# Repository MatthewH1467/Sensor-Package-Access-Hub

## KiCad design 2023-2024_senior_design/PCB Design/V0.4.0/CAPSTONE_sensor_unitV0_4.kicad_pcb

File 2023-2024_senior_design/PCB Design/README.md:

# PCB Design

## V0.3.0
* All components on board

## V0.4.0
* Add holes for standoffs
* Compress board size
* Added silkscreen logo, designer names, part names, version number, 
* Add a ground plane
* Different footprint for Teensy

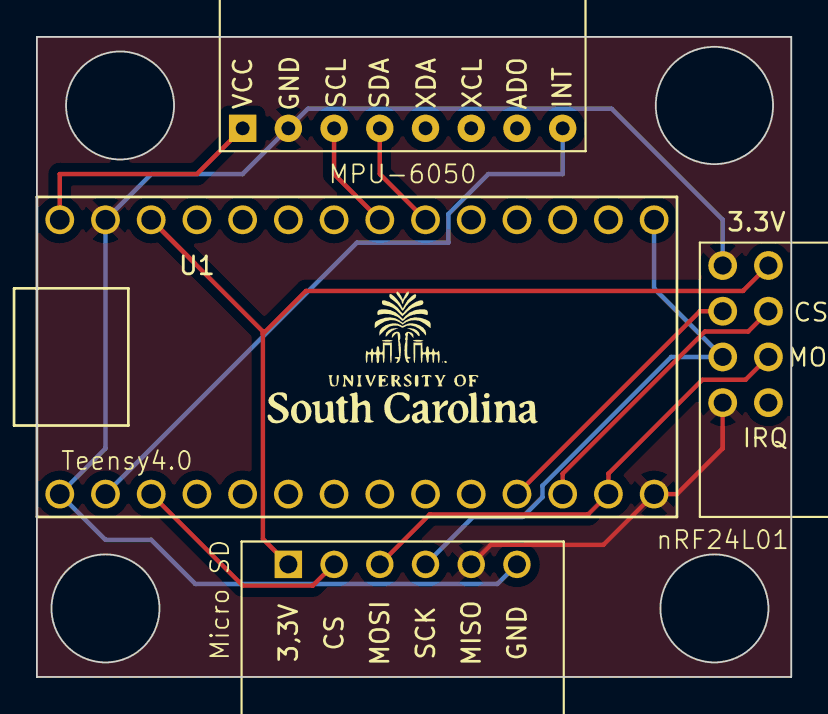
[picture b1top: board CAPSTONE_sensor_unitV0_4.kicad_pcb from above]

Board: 2 copper layers, 41.9 x 35.6 mm, 4 parts (0 on the bottom side), 12 nets.

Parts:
MPU-6050: MPU6050_Module; MPU6050_Sensor_package_edit
Micro SD: microSD_small-ARTS-Lab; small_microSD_sensor_package_edit
U1: Teensy4.0-teensy-ARTS-Lab; Teensy40_sensor_package_edit
nRF24L01: nRF24L01+-ARTS-Lab; nRF24L01+_sensor_package_edit_V0_2

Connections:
GND: MPU-6050.2 (GND), Micro SD.6 (GND), U1.1 (GND), U1.32 (GND), nRF24L01.5 (GND)
unnamed: MPU-6050.8 (INT), U1.2 (0_RX1_CRX2_CS1)
unnamed: MPU-6050.3 (SCL), U1.26 (19_A5_SCL0)
unnamed: MPU-6050.4 (SDA), U1.25 (18_A4_SDA0)
unnamed: MPU-6050.1 (VCC), U1.33 (VIN)
unnamed: Micro SD.1 (3.3V), U1.31 (3V3), nRF24L01.1 (3.3V)
unnamed: Micro SD.4 (CLK), U1.20 (13_SCK_CRX1_LED), nRF24L01.7 (SCK)
unnamed: Micro SD.2 (CS), U1.3 (1_TX1_CTX2_MISO1)
unnamed: Micro SD.5 (MISO), U1.14 (12_MISO_MQSL), nRF24L01.8 (MISO)
unnamed: Micro SD.3 (MOSI), U1.13 (11_MOSI_CTX1), nRF24L01.3 (MOSI)
unnamed: U1.11 (9_OUT1C), nRF24L01.6 (CE)
unnamed: U1.12 (10_CS_MQSR), nRF24L01.2 (CSN)

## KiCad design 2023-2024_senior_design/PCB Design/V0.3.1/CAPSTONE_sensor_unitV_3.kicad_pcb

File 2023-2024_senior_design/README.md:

# Sensor-Package-Access-Hub (2023-2024 Senior Design Project)
1. xxx

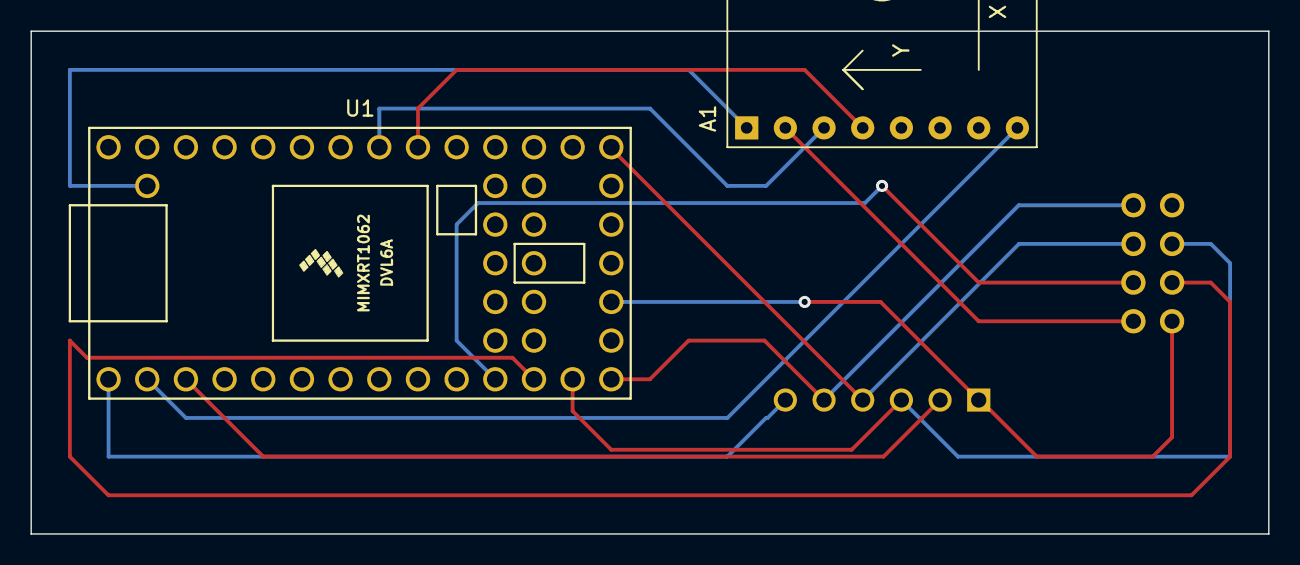
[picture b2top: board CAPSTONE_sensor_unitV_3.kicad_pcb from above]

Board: 2 copper layers, 81.3 x 33.0 mm, 4 parts (0 on the bottom side), 13 nets.

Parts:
A1: MPU6050_Module
Micro_SD1: microSD_small-ARTS-Lab; small_microSD_v2
U1: Teensy4.0-teensy-ARTS-Lab; Teensy40
U2: nRF24L01+-ARTS-Lab; nRF24L01+

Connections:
unnamed: A1.2 (GND), U2.5 (GND)
unnamed: A1.8 (INT), U1.2 (0_RX1_CRX2_CS1)
unnamed: A1.3 (SCL), U1.26 (19_A5_SCL0)
unnamed: A1.4 (SDA), U1.25 (18_A4_SDA0)
unnamed: A1.1 (VCC), U1.34 (VUSB)
unnamed: Micro_SD1.1 (3.3V), U1.16 (3V3), U2.1 (3.3V)
unnamed: Micro_SD1.4 (CLK), U1.20 (13_SCK_CRX1_LED), U2.7 (SCK)
unnamed: Micro_SD1.2 (CS), U1.3 (1_TX1_CTX2_MISO1)
unnamed: Micro_SD1.6 (GND), U1.1 (GND)
unnamed: Micro_SD1.5 (MISO), U1.14 (12_MISO_MQSL), U2.8 (MISO)
unnamed: Micro_SD1.3 (MOSI), U1.13 (11_MOSI_CTX1), U2.3 (MOSI)
unnamed: U1.11 (9_OUT1C), U2.6 (CE)
unnamed: U1.12 (10_CS_MQSR), U2.2 (CSN)

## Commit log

2023-05-02 transmission of a single data point
    These files, with the exception of the CSV reader, may be used for the transmission of a single data point from a teensy sensor package to a Pi. The CSV reader is the beginnings of a modified master 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
2023-05-02 Create Master_README
2023-05-02 Create Package_README
2023-06-02 made readme markdown files
2023-11-07 WIP Sensor Package Subsystem Code
2023-11-21 PCB design for Sensor package 1st Iteration
2023-11-21 Libraries For Sensor PCB
2023-11-21 Updates on PCB file structure
2023-11-21 remaned folder
2023-12-01 PCB Design V0.4.0
